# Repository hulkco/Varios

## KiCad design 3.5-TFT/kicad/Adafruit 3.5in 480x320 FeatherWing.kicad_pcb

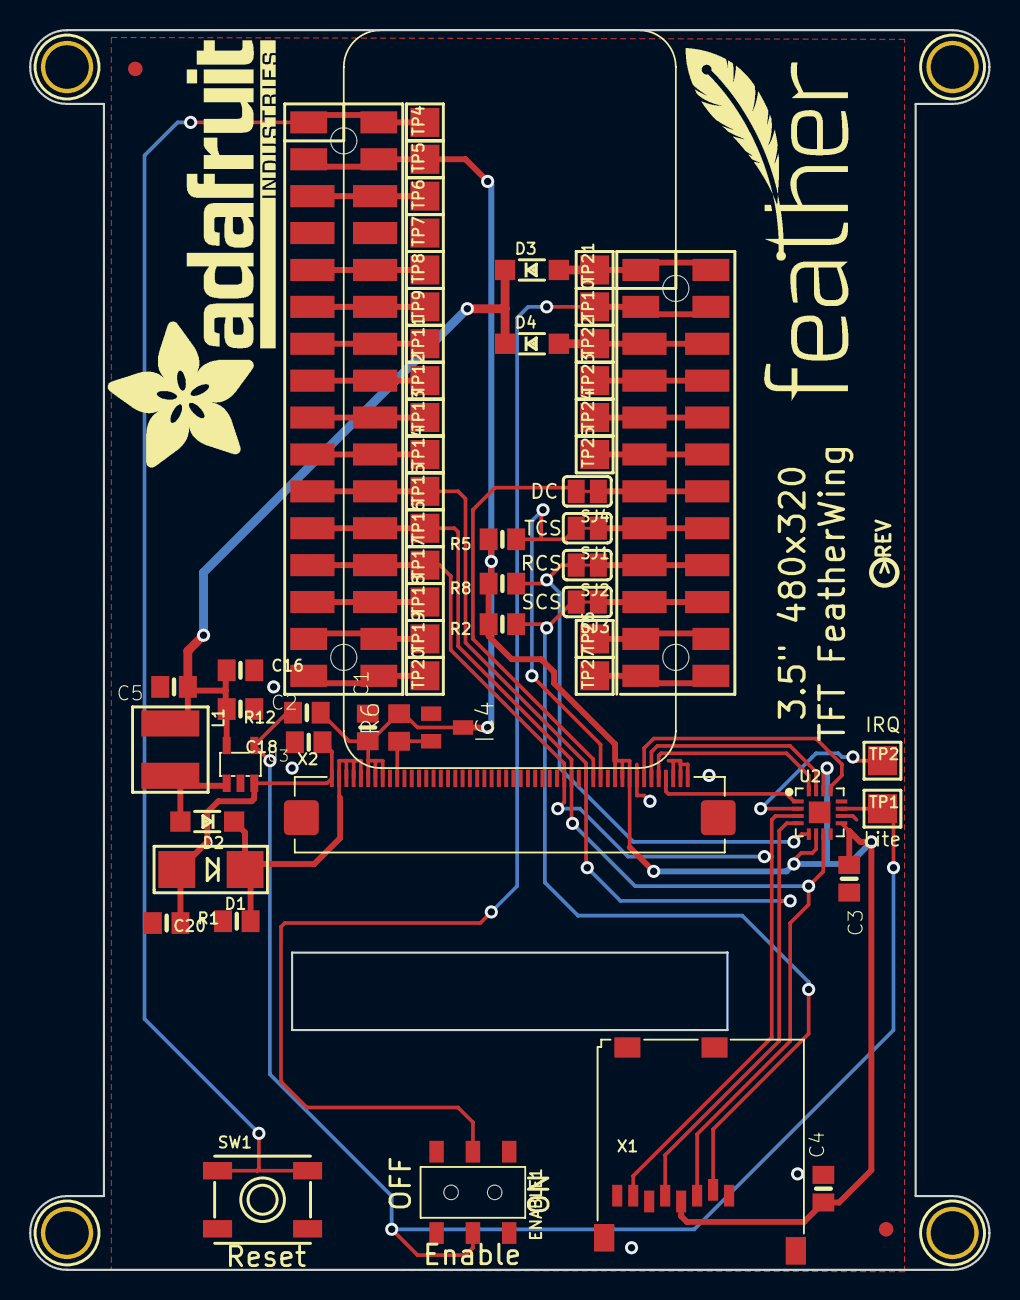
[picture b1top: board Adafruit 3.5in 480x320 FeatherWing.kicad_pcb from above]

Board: 16 copper layers, 66.0 x 85.3 mm, 66 parts (0 on the bottom side), 43 nets.

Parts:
C1, C16, C20: 1uF; 0805-NO
C2, C3, C4, C5: 10uF; 0805-NO
C18: 0.1uF; 0805-NO
D1: MM3Z24VT1G; SMADIODE
D2: MBR0540; SOD-123
D3, D4: MBR120; SOD-123
ENABLE1: Slide Switch; EG1390
IC4: APX803-SAG; SOT23
L1: 15uH; INDUCTOR_5X5MM_NR5040_NOTHERMALS
MS2: FEATHERWING_SMTDUAL; FEATHERWING_SMT2
R1: 12Ω; 0805-NO
R2, R5, R8: 100K; 0805-NO
R6: 10K; R0805
R12: 10K; 0805-NO
SJ1, SJ2, SJ3, SJ4: SOLDERJUMPER_CLOSED; SOLDERJUMPER_CLOSEDWIRE
SW1: EVQQ2; EVQ-Q2_SMALLER
TP1, TP2, TP4, TP5, TP6, TP7, TP8, TP9, TP10, TP11, TP12, TP13, TP14, TP15, TP16, TP17, TP18, TP19, TP20, TP21, TP22, TP23, TP24, TP25, TP26, TP27: TESTPOINTPAD2MM; TESTPOINT_PAD_2MM
U2: STMPE811; QFN16_3MM
U3: FAN5333BSX; SOT23-5@1
U$7, U$15, U$16, U$17: MOUNTINGHOLE3.0THIN; MOUNTINGHOLE_3.0_PLATEDTHIN
U$9, U$23: FIDUCIAL_1MM
U$11: FEATHERLOGO
U$19: ADAFRUIT_TEXT_30MM
U$37: PCBFEAT-REV-040
X1: MicroSD; MICROSD
X2: 3.5" TFT; TFT_3.5IN_320X480_50PIN

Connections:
3.3V: C1.1, C3.1, C4.1, IC4.3, MS2.2, MS2.2', R2.2, R5.2, R6.2, R8.2, R12.1, TP5.P$1, U2.6, U2.9, U2.14, X1.4, X2.6, X2.7, X2.8, X2.40, X2.41, X2.42
+5V: C2.1, C5.1, C16.1, D3.C, D4.C, L1.P$1, U3.5
+24V: C20.1, D1.C, D2.C, X2.2, X2.3, X2.4, X2.5
/EN: ENABLE1.P2, MS2.27, MS2.27', TP10.P$1
/LCD_LITE: ENABLE1.P1, R12.2, TP1.P$1, U2.11, U3.4
/LEDK: C18.1, D1.A, R1.2, U3.3, X2.1
/MISO: MS2.13, MS2.13', TP17.P$1, U2.3, X1.7, X2.33
/MOSI: MS2.12, MS2.12', TP16.P$1, U2.7, X1.3, X2.34
/RT_CS: R8.1, SJ2.2, U2.5
/RT_INT: TP2.P$1, U2.2
/SCLK: MS2.11, MS2.11', TP15.P$1, U2.4, X1.5, X2.36
/SD_CS: R2.1, SJ3.2, X1.2
/TFT_CS: R5.1, SJ1.2, X2.38
/TFT_DC: SJ4.2, X2.37
/XL: U2.16, X2.46
/XR: U2.13, X2.44
/YD: U2.15, X2.45
/YU: U2.1, X2.47
/~TFT_RST: IC4.2, R6.1, X2.10
GND: C1.2, C2.2, C3.2, C4.2, C5.2, C16.2, C18.2, C20.2, ENABLE1.S1, ENABLE1.S2, IC4.1, MS2.4, MS2.4', R1.1, SW1.A, SW1.A', TP7.P$1, U2.10, U3.2, X1.6, X1.MT1, X1.MT2, X2.43, X2.48, X2.49, X2.50
unnamed: D2.A, L1.P$2, U3.1
unnamed: D3.A, MS2.28, MS2.28', TP21.P$1
unnamed: D4.A, MS2.26, MS2.26', TP22.P$1
unnamed: MS2.1, MS2.1', SW1.B, SW1.B', TP4.P$1
unnamed: MS2.3, MS2.3', TP6.P$1
unnamed: MS2.5, MS2.5', TP8.P$1
unnamed: MS2.6, MS2.6', TP9.P$1
unnamed: MS2.7, MS2.7', TP11.P$1
unnamed: MS2.8, MS2.8', TP12.P$1
unnamed: MS2.9, MS2.9', TP13.P$1
unnamed: MS2.10, MS2.10', TP14.P$1
unnamed: MS2.14, MS2.14', TP18.P$1
unnamed: MS2.15, MS2.15', TP19.P$1
unnamed: MS2.16, MS2.16', TP20.P$1
unnamed: MS2.17, MS2.17', TP27.P$1
unnamed: MS2.18, MS2.18', TP26.P$1
unnamed: MS2.19, MS2.19', SJ3.1
unnamed: MS2.20, MS2.20', SJ2.1
unnamed: MS2.21, MS2.21', SJ1.1
unnamed: MS2.22, MS2.22', SJ4.1
unnamed: MS2.23, MS2.23', TP25.P$1
unnamed: MS2.24, MS2.24', TP24.P$1
unnamed: MS2.25, MS2.25', TP23.P$1

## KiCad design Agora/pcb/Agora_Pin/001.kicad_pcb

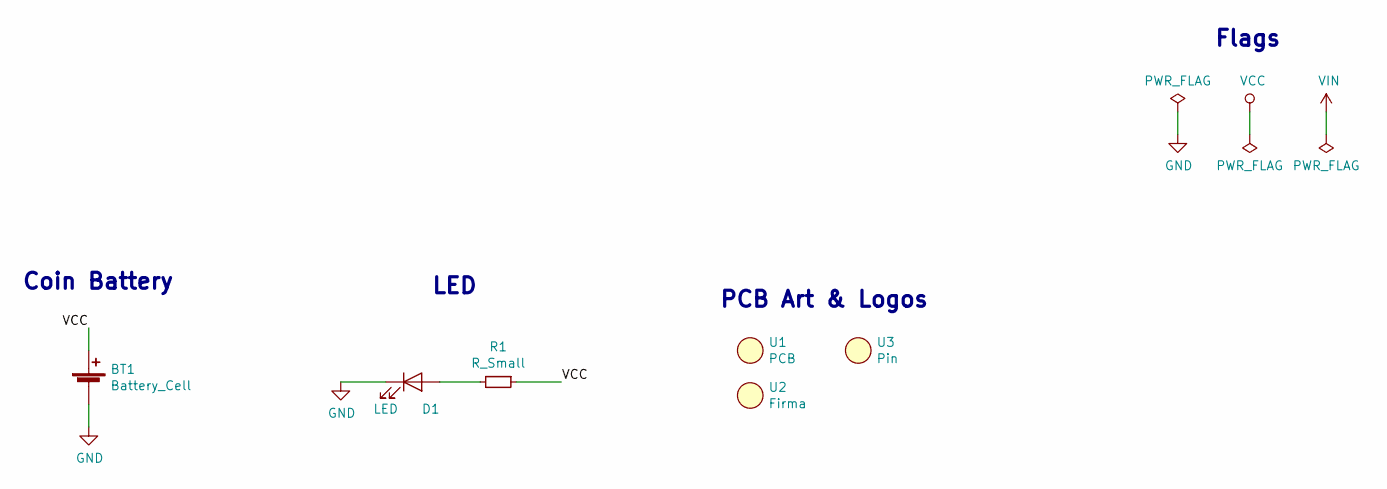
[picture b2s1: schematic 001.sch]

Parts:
BT1: Battery_Cell; S8211R
D1: LED; L_1206_3216Metric_Pad1.42x1.75mm_HandSolder
R1: R_Small; R_1206_3216Metric_Pad1.42x1.75mm_HandSolder
U1: PCB; agora_pin_001_46.5mm
U2: Firma; firma_Cu_Mask
U3: Pin; Codi_Pin_Pad_D5.0mm

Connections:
GND: BT1.2 (-), D1.1 (K)
unnamed: D1.2 (A), R1.2
VCC: BT1.1 (+), R1.1

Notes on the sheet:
LED
Coin Battery
Flags
PCB Art & Logos

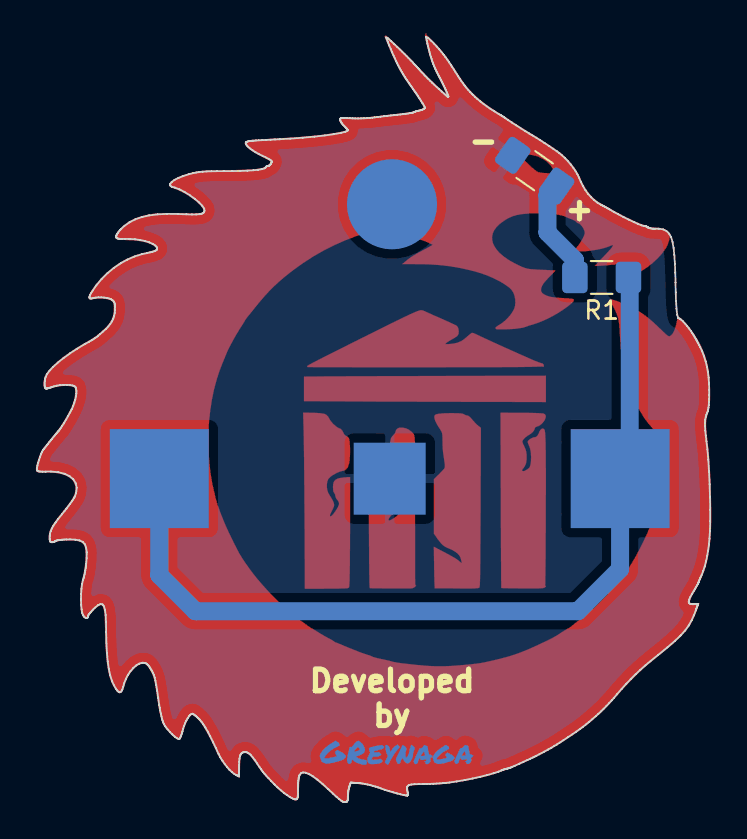
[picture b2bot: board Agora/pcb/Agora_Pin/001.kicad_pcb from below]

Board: 2 copper layers, 37.4 x 42.5 mm, 6 parts (5 on the bottom side), 3 nets.

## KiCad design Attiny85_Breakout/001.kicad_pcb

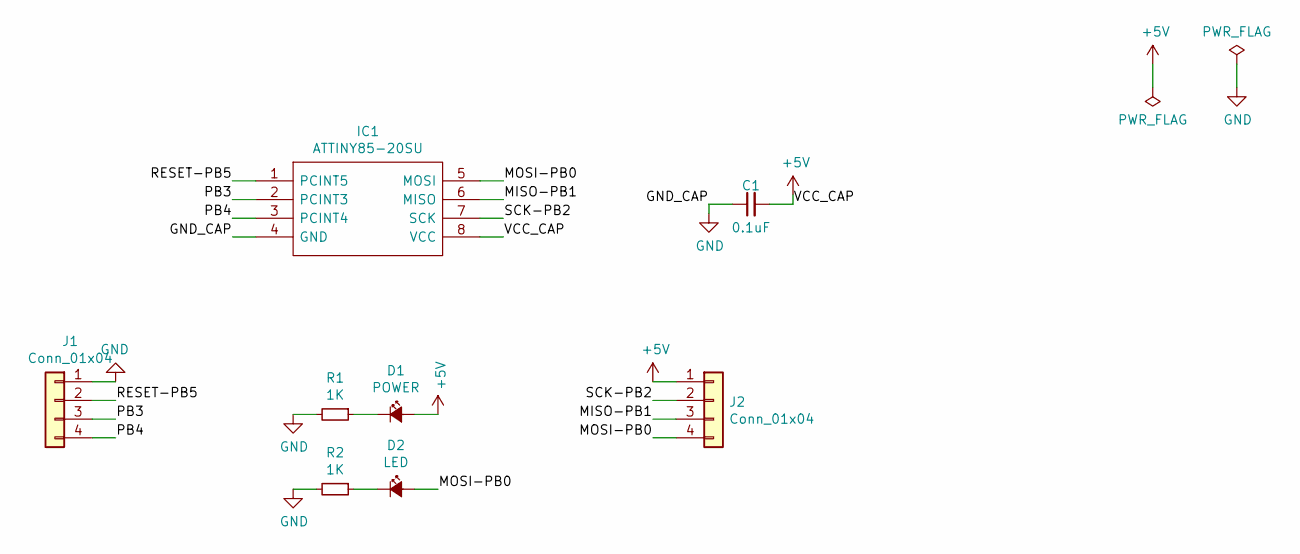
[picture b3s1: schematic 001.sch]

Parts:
C1: 0.1uF; C_1206_3216Metric_Pad1.42x1.75mm_HandSolder
D1: POWER; LED_1206_3216Metric_Pad1.42x1.75mm_HandSolder
D2: LED; LED_1206_3216Metric_Pad1.42x1.75mm_HandSolder
IC1: ATTINY85-20SU; SOT127P798X216-8N; Mouser Part Number 556-ATTINY85-20SU
J1, J2: Conn_01x04; PinHeader_1x04_P2.54mm_Vertical
R1, R2: 1K; R_1206_3216Metric_Pad1.42x1.75mm_HandSolder

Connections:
+5V: C1.2, D1.2 (A), IC1.8 (VCC), J2.1
/MISO-PB1: IC1.6 (MISO), J2.3
/MOSI-PB0: D2.2 (A), IC1.5 (MOSI), J2.4
/PB3: IC1.2 (PCINT3), J1.3
/PB4: IC1.3 (PCINT4), J1.4
/RESET-PB5: IC1.1 (PCINT5), J1.2
/SCK-PB2: IC1.7 (SCK), J2.2
GND: C1.1, IC1.4 (GND), J1.1, R1.2, R2.2
unnamed: D1.1 (K), R1.1
unnamed: D2.1 (K), R2.1

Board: 2 copper layers, 9 parts (0 on the bottom side), 10 nets, no tracks yet.

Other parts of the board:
Ref**: Val**; Breakout_Attiny85_01

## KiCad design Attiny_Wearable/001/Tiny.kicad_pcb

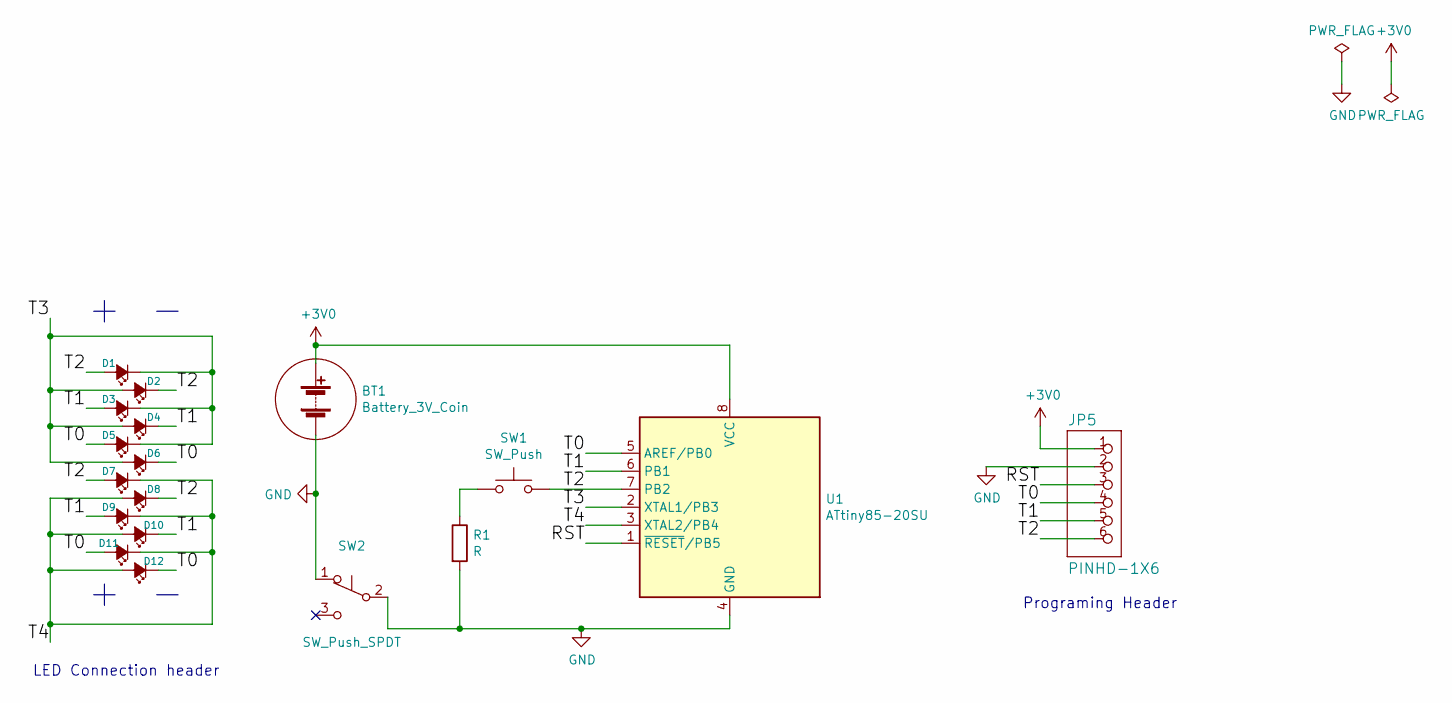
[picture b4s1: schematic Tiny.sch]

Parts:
BT1: Battery_3V_Coin; S8211R
D1, D2, D3, D4, D5, D6, D7, D8, D9, D10, D11, D12: LED_Small_ALT; LED_1206_3216Metric_Pad1.42x1.75mm_HandSolder
JP5: PINHD-1X6; PogoPinSocket_2x03_P2.54mm
R1: R; R_1206_3216Metric_Pad1.42x1.75mm_HandSolder
SW1: SW_Push; SW_SPST_B3U-1000P
SW2: SW_Push_SPDT; SW_SPDT_PCM12
U1: ATtiny85-20SU; SOIJ-8_5.3x5.3mm_P1.27mm

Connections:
+3V0: BT1.1 (+), JP5.1, U1.8 (VCC)
/RST: JP5.3, U1.1 (~RESET~/PB5)
/T0: D5.2 (A), D6.1 (K), D11.2 (A), D12.1 (K), JP5.4, U1.5 (AREF/PB0)
/T1: D3.2 (A), D4.1 (K), D9.2 (A), D10.1 (K), JP5.5, U1.6 (PB1)
/T2: D1.2 (A), D2.1 (K), D7.2 (A), D8.1 (K), JP5.6, SW1.2, U1.7 (PB2)
/T3: D1.1 (K), D2.2 (A), D3.1 (K), D4.2 (A), D5.1 (K), D6.2 (A), U1.2 (XTAL1/PB3)
/T4: D7.1 (K), D8.2 (A), D9.1 (K), D10.2 (A), D11.1 (K), D12.2 (A), U1.3 (XTAL2/PB4)
GND: BT1.2 (-), JP5.2, R1.2, SW2.1 (A), SW2.2 (B), U1.4 (GND)
unnamed: R1.1, SW1.1

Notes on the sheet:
Programing Header
LED Connection header

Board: 2 copper layers, 19 parts (0 on the bottom side), 9 nets, no tracks yet.

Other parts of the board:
Ref**: Val**; cody
